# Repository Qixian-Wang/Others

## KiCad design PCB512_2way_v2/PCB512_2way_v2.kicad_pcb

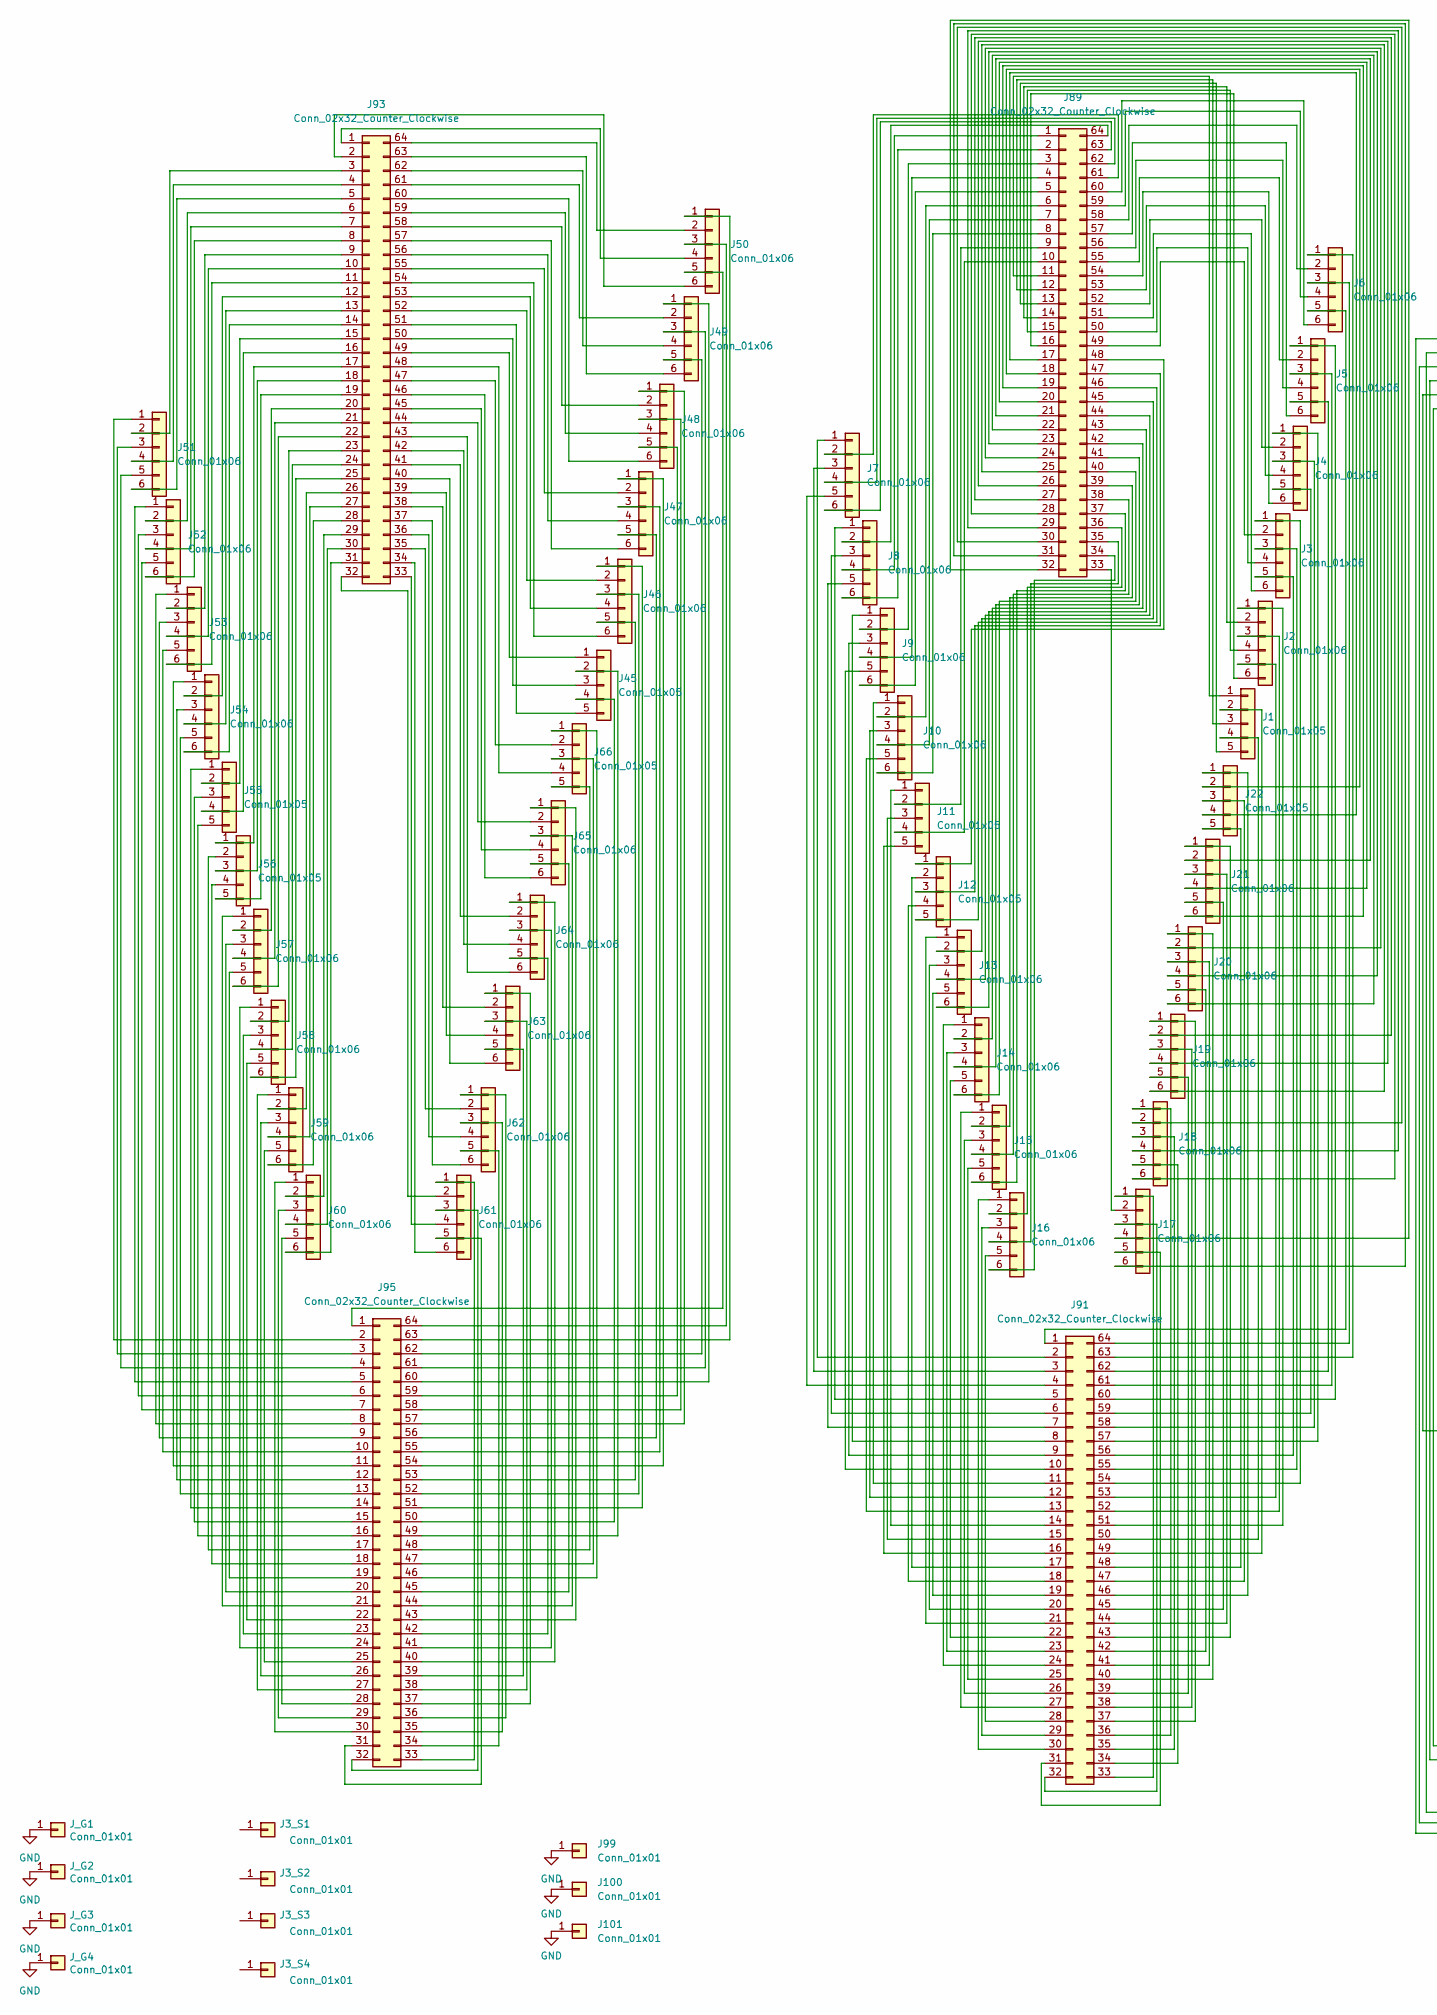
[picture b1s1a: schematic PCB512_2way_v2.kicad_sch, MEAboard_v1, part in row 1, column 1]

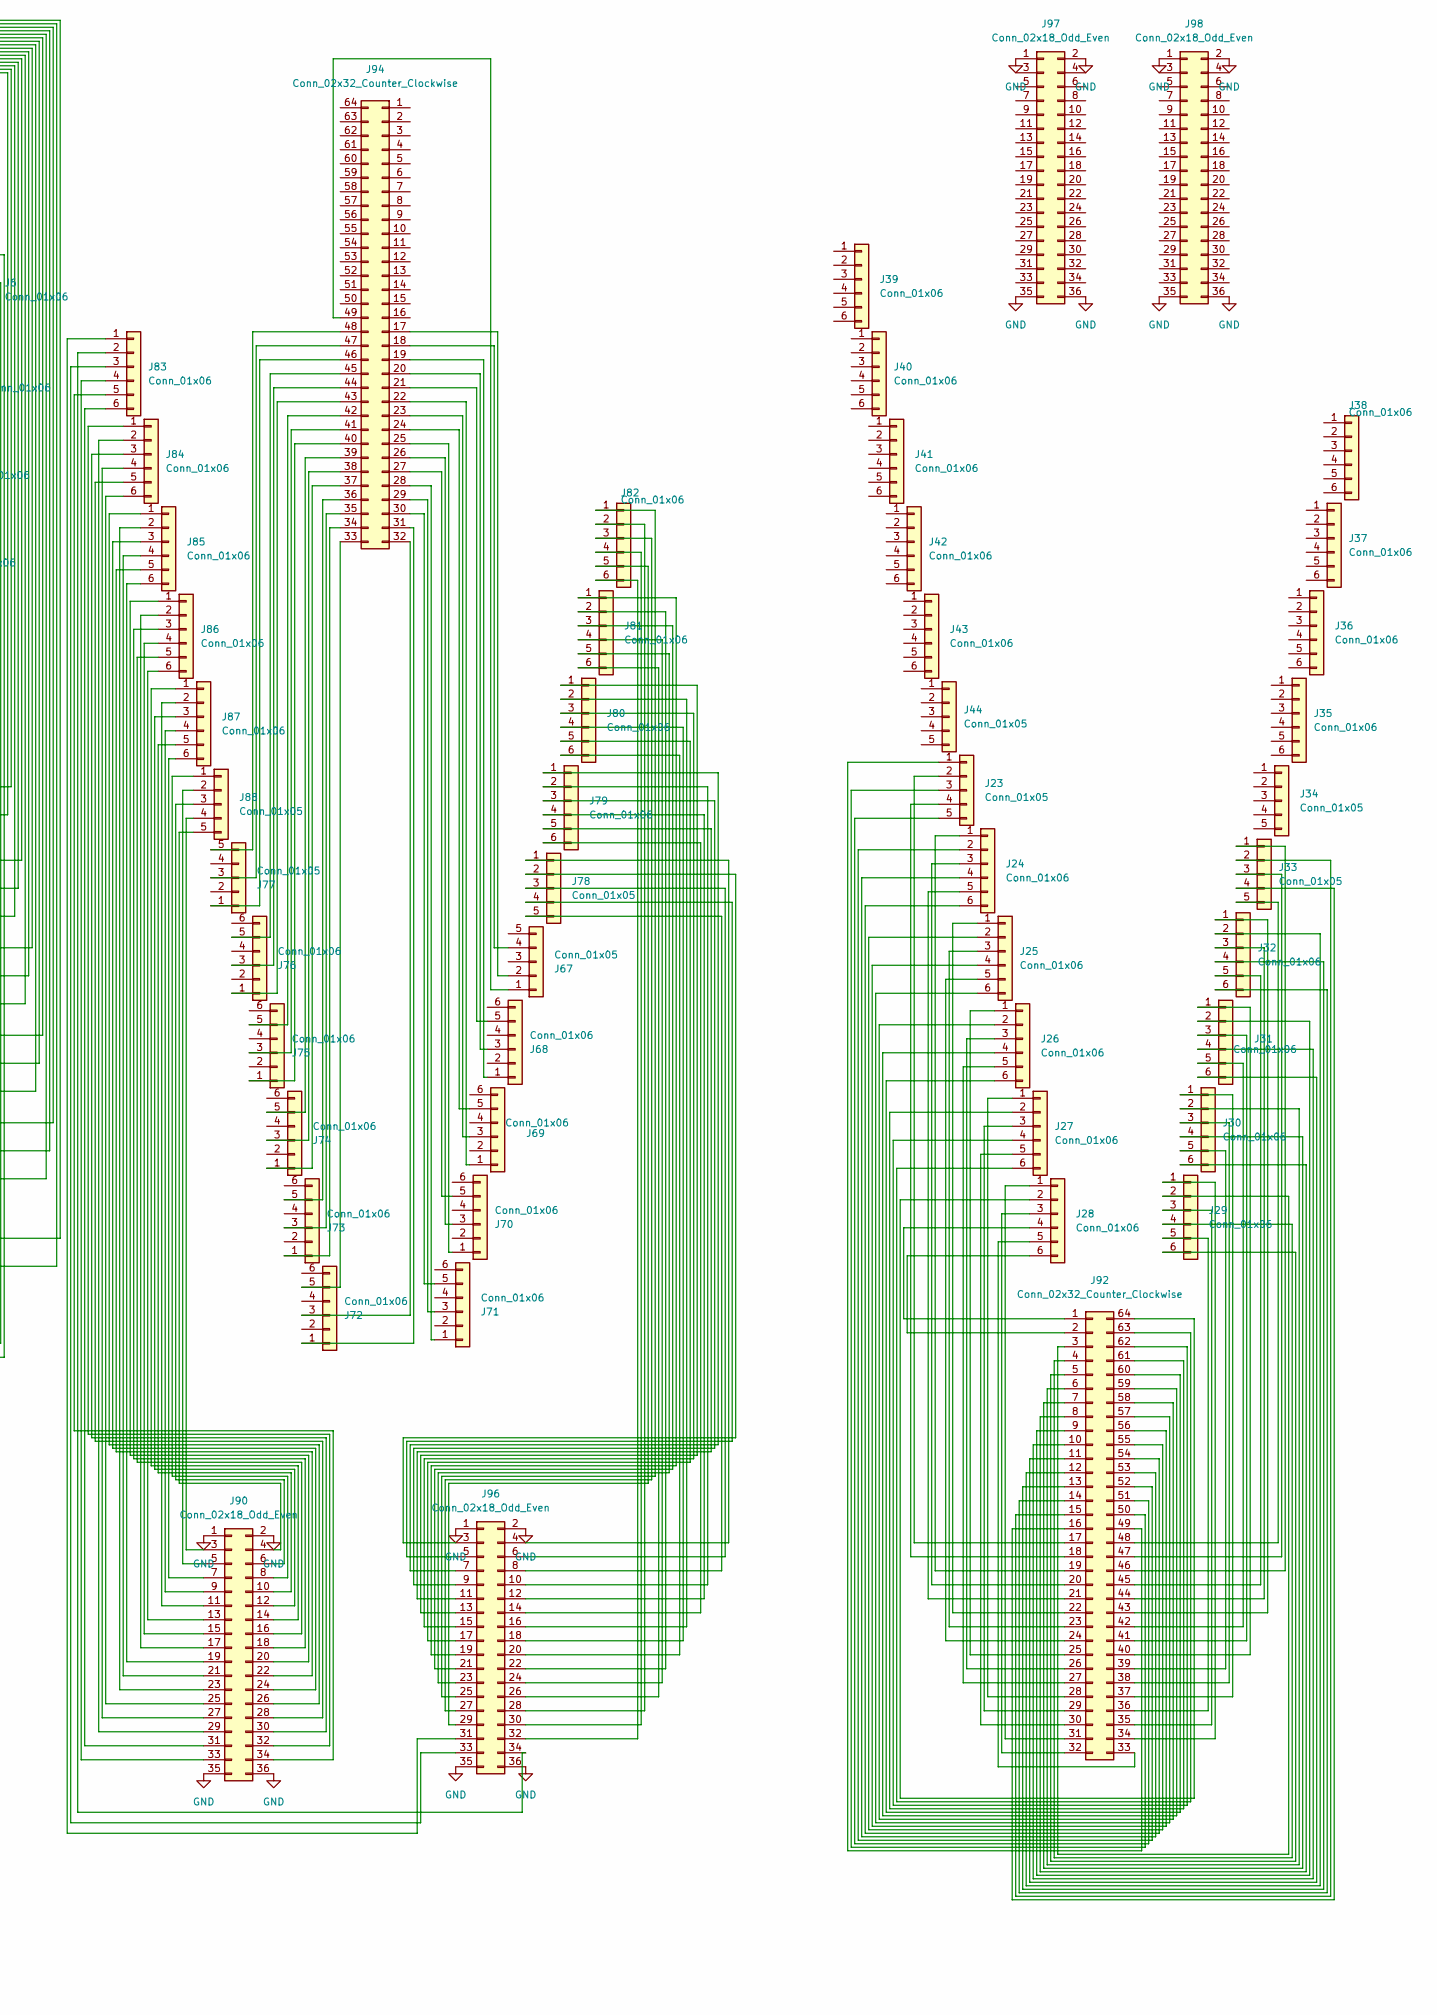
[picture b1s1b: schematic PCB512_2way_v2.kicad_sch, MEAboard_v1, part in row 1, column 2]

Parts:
J1, J11, J12, J22, J23, J33, J34, J44, J45, J55, J56, J66, J67, J77, J78, J88: Conn_01x05; PinHeader_1x05_P1.5mm_Vertical
J2, J3, J4, J5, J6, J7, J8, J9, J10, J13, J14, J15, J16, J17, J18, J19, J20, J21, J24, J25, J26, J27, J28, J29, J30, J31, J32, J35, J36, J37, J38, J39, J40, J41, J42, J43, J46, J47, J48, J49, J50, J51, J52, J53, J54, J57, J58, J59, J60, J61, J62, J63, J64, J65, J68, J69, J70, J71, J72, J73, J74, J75, J76, J79, J80, J81, J82, J83, J84, J85, J86, J87: Conn_01x06; PinHeader_1x06_P1.5mm_Vertical
J3_S1, J3_S2, J3_S3, J3_S4: Conn_01x01; PinHeader_1x01_P1.27mm_Vertical_0.483_STIM
J89, J91, J92, J93: Conn_02x32_Counter_Clockwise; PinHeader_2x32_P0.4mm_Vertical_SMD_Molex_Back
J90, J98: Conn_02x18_Odd_Even; PinHeader_2x18_Omnetics_Vertical_Hole_SMD_right_back
J94, J95: Conn_02x32_Counter_Clockwise; PinHeader_2x32_P0.4mm_Vertical_SMD_Molex
J96, J97: Conn_02x18_Odd_Even; PinHeader_2x18_Omnetics_Vertical_Hole_SMD_left_back
J99, J100, J101: Conn_01x01; PinSocket_1x01_P1.27mm_Vertical
J_G1, J_G2, J_G3, J_G4: Conn_01x01; PinHeader_1x01_P1.27mm_Vertical_0.483_GND

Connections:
GND: J90.1, J90.2, J90.35, J90.36, J96.1, J96.2, J96.35, J96.36, J97.1, J97.2, J97.35, J97.36, J98.1, J98.2, J98.35, J98.36, J99.1, J100.1, J101.1, J_G1.1, J_G2.1, J_G3.1, J_G4.1; also elsewhere on the board
unnamed: J1.1, J89.11
unnamed: J1.2, J91.49
unnamed: J1.3, J89.12
unnamed: J1.4, J91.50
unnamed: J1.5, J89.13
unnamed: J2.1, J91.51
unnamed: J2.2, J89.14
unnamed: J2.3, J91.52
unnamed: J2.4, J89.15
unnamed: J2.5, J91.53
unnamed: J2.6, J89.16
unnamed: J3.1, J91.54
unnamed: J3.2, J89.49
unnamed: J3.3, J91.55
unnamed: J3.4, J89.50
unnamed: J3.5, J91.56
unnamed: J3.6, J89.51
unnamed: J4.1, J91.57
unnamed: J4.2, J89.52
unnamed: J4.3, J91.58
unnamed: J4.4, J89.53
unnamed: J4.5, J91.59
unnamed: J4.6, J89.54
unnamed: J5.1, J91.60
unnamed: J5.2, J89.55
unnamed: J5.3, J91.61
unnamed: J5.4, J89.56
unnamed: J5.5, J91.62
unnamed: J5.6, J89.57
unnamed: J6.1, J91.63
unnamed: J6.2, J89.58
unnamed: J6.3, J91.64
unnamed: J6.4, J89.59
unnamed: J6.5, J91.1
unnamed: J6.6, J89.60
unnamed: J7.1, J91.2
unnamed: J7.2, J89.61
unnamed: J7.3, J91.3
unnamed: J7.4, J89.62
unnamed: J7.5, J91.4
unnamed: J7.6, J89.63
unnamed: J8.1, J91.5
unnamed: J8.2, J89.64
unnamed: J8.3, J91.6
unnamed: J8.4, J89.1
unnamed: J8.5, J91.7
unnamed: J8.6, J89.2
unnamed: J9.1, J91.8
unnamed: J9.3, J91.9
unnamed: J9.5, J91.10
unnamed: J10.1, J91.11
unnamed: J10.2, J89.6
unnamed: J10.3, J91.12
unnamed: J10.4, J89.7
unnamed: J10.5, J91.13
unnamed: J10.6, J89.8
unnamed: J11.1, J91.14
unnamed: J11.2, J89.9
unnamed: J11.3, J91.15
unnamed: J11.4, J89.10
unnamed: J11.5, J91.16
unnamed: J12.1, J89.48
unnamed: J12.2, J91.17
unnamed: J12.3, J89.47
unnamed: J12.4, J91.18
unnamed: J12.5, J89.46
unnamed: J13.1, J91.21
unnamed: J13.2, J89.45
unnamed: J13.3, J91.20
unnamed: J13.4, J89.44
unnamed: J13.5, J91.19
unnamed: J13.6, J89.43
unnamed: J14.1, J91.24
unnamed: J14.2, J89.42
unnamed: J14.3, J91.23
unnamed: J14.4, J89.41
unnamed: J14.5, J91.22
unnamed: J14.6, J89.40
unnamed: J15.1, J91.27
unnamed: J15.2, J89.39
unnamed: J15.3, J91.26
unnamed: J15.4, J89.38
unnamed: J15.5, J91.25
unnamed: J15.6, J89.37
unnamed: J16.1, J91.30
unnamed: J16.2, J89.36
unnamed: J16.3, J91.29
unnamed: J16.4, J89.35
unnamed: J16.5, J91.28
unnamed: J16.6, J89.34
unnamed: J17.1, J91.33
unnamed: J17.2, J89.33
unnamed: J17.3, J91.32
unnamed: J17.4, J89.32
unnamed: J17.5, J91.31
unnamed: J17.6, J89.31
unnamed: J18.1, J91.36
unnamed: J18.2, J89.30
unnamed: J18.3, J91.35
unnamed: J18.4, J89.29
unnamed: J18.5, J91.34
unnamed: J18.6, J89.28
unnamed: J19.1, J91.37
unnamed: J19.2, J89.27
unnamed: J19.3, J91.38
unnamed: J19.4, J89.26
unnamed: J19.5, J91.39
unnamed: J19.6, J89.25
unnamed: J20.1, J91.40
unnamed: J20.2, J89.24
unnamed: J20.3, J91.41
unnamed: J20.4, J89.23
unnamed: J20.5, J91.42
unnamed: J20.6, J89.22
unnamed: J21.1, J91.43
unnamed: J21.2, J89.21
unnamed: J21.3, J91.44
unnamed: J21.4, J89.20
unnamed: J21.5, J91.45
unnamed: J21.6, J89.19
unnamed: J22.1, J91.46
unnamed: J22.2, J89.18
unnamed: J22.3, J91.47
unnamed: J22.4, J89.17
unnamed: J22.5, J91.48
unnamed: J23.1, J92.49
unnamed: J23.2, J92.17
unnamed: J23.3, J92.50
unnamed: J23.4, J92.18
unnamed: J23.5, J92.51
unnamed: J24.1, J92.19
unnamed: J24.2, J92.52
unnamed: J24.3, J92.20
unnamed: J24.4, J92.53
unnamed: J24.5, J92.21
unnamed: J24.6, J92.54
unnamed: J25.1, J92.22
unnamed: J25.2, J92.55
unnamed: J25.3, J92.23
unnamed: J25.4, J92.56
unnamed: J25.5, J92.24
unnamed: J25.6, J92.57
unnamed: J26.1, J92.25
unnamed: J26.2, J92.58
unnamed: J26.3, J92.26
unnamed: J26.4, J92.59
unnamed: J26.5, J92.27
unnamed: J26.6, J92.60
unnamed: J27.1, J92.28
unnamed: J27.2, J92.61
unnamed: J27.3, J92.29
unnamed: J27.4, J92.62
unnamed: J27.5, J92.30
unnamed: J27.6, J92.63
unnamed: J28.1, J92.31
unnamed: J28.2, J92.64
unnamed: J28.3, J92.32
unnamed: J28.4, J92.1
unnamed: J28.5, J92.33
unnamed: J28.6, J92.2
unnamed: J29.1, J92.34
unnamed: J29.2, J92.3
unnamed: J29.3, J92.35
unnamed: J29.4, J92.4
unnamed: J29.5, J92.36
unnamed: J29.6, J92.5
unnamed: J30.1, J92.37
unnamed: J30.2, J92.6
unnamed: J30.3, J92.38
unnamed: J30.4, J92.7
unnamed: J30.5, J92.39
unnamed: J30.6, J92.8
unnamed: J31.1, J92.40
unnamed: J31.2, J92.9
unnamed: J31.3, J92.41
unnamed: J31.4, J92.10
unnamed: J31.5, J92.42
unnamed: J31.6, J92.11
unnamed: J32.1, J92.43
unnamed: J32.2, J92.12
unnamed: J32.3, J92.44
unnamed: J32.4, J92.13
unnamed: J32.5, J92.45
unnamed: J32.6, J92.14
unnamed: J33.1, J92.46
unnamed: J33.2, J92.15
unnamed: J33.3, J92.47
unnamed: J33.4, J92.16
unnamed: J33.5, J92.48
unnamed: J45.1, J93.49
unnamed: J45.2, J95.49
unnamed: J45.3, J93.50
unnamed: J45.4, J95.50
unnamed: J45.5, J93.51
unnamed: J46.1, J95.51
unnamed: J46.2, J93.52
unnamed: J46.3, J95.52
unnamed: J46.4, J93.53
unnamed: J46.5, J95.53
unnamed: J46.6, J93.54
unnamed: J47.1, J95.54
unnamed: J47.2, J93.55
unnamed: J47.3, J95.55
unnamed: J47.4, J93.56
unnamed: J47.5, J95.56
unnamed: J47.6, J93.57
unnamed: J48.1, J95.57
unnamed: J48.2, J93.58
unnamed: J48.3, J95.58
unnamed: J48.4, J93.59
unnamed: J48.5, J95.59
unnamed: J48.6, J93.60
unnamed: J49.1, J95.60
unnamed: J49.2, J93.61
unnamed: J49.3, J95.61
unnamed: J49.4, J93.62
unnamed: J49.5, J95.62
unnamed: J49.6, J93.63
unnamed: J50.1, J95.63
unnamed: J50.2, J93.64
unnamed: J50.3, J95.64
unnamed: J50.4, J93.1
unnamed: J50.5, J95.1
unnamed: J50.6, J93.2
unnamed: J51.1, J95.2
unnamed: J51.2, J93.3
unnamed: J51.3, J95.3
unnamed: J51.4, J93.4
unnamed: J51.5, J95.4
unnamed: J51.6, J93.5
unnamed: J52.1, J95.5
unnamed: J52.2, J93.6
unnamed: J52.3, J95.6
unnamed: J52.4, J93.7
unnamed: J52.5, J95.7
unnamed: J52.6, J93.8
unnamed: J53.1, J95.8
unnamed: J53.2, J93.9
unnamed: J53.3, J95.9
unnamed: J53.4, J93.10
unnamed: J53.5, J95.10
unnamed: J53.6, J93.11
unnamed: J54.1, J95.11
unnamed: J54.2, J93.12
unnamed: J54.3, J95.12
unnamed: J54.4, J93.13
unnamed: J54.5, J95.13
unnamed: J54.6, J93.14
unnamed: J55.1, J95.14
unnamed: J55.2, J93.15
unnamed: J55.3, J95.15
unnamed: J55.4, J93.16
unnamed: J55.5, J95.16
unnamed: J56.1, J93.17
unnamed: J56.2, J95.17
unnamed: J56.3, J93.18
unnamed: J56.4, J95.18
unnamed: J56.5, J93.19
unnamed: J57.1, J95.21
unnamed: J57.2, J93.20
unnamed: J57.3, J95.20
unnamed: J57.4, J93.21
unnamed: J57.5, J95.19
unnamed: J57.6, J93.22
unnamed: J58.1, J95.24
unnamed: J58.2, J93.23
unnamed: J58.3, J95.23
unnamed: J58.4, J93.24
unnamed: J58.5, J95.22
unnamed: J58.6, J93.25
unnamed: J59.1, J95.27
unnamed: J59.2, J93.26
unnamed: J59.3, J95.26
unnamed: J59.4, J93.27
unnamed: J59.5, J95.25
unnamed: J59.6, J93.28
unnamed: J60.1, J95.30
unnamed: J60.2, J93.29
unnamed: J60.3, J95.29
unnamed: J60.4, J93.30
unnamed: J60.5, J95.28
unnamed: J60.6, J93.31
unnamed: J61.1, J95.33
unnamed: J61.2, J93.32
unnamed: J61.3, J95.32
unnamed: J61.4, J93.33
unnamed: J61.5, J95.31
unnamed: J61.6, J93.34
unnamed: J62.1, J95.36
unnamed: J62.2, J93.35
unnamed: J62.3, J95.35
unnamed: J62.4, J93.36
unnamed: J62.5, J95.34
unnamed: J62.6, J93.37
unnamed: J63.1, J95.37
unnamed: J63.2, J93.38
unnamed: J63.3, J95.38
unnamed: J63.4, J93.39
unnamed: J63.5, J95.39
unnamed: J63.6, J93.40
unnamed: J64.1, J95.40
unnamed: J64.2, J93.41
unnamed: J64.3, J95.41
unnamed: J64.4, J93.42
unnamed: J64.5, J95.42
unnamed: J64.6, J93.43
unnamed: J65.1, J95.43
unnamed: J65.2, J93.44
unnamed: J65.3, J95.44
unnamed: J65.4, J93.45
unnamed: J65.5, J95.45
unnamed: J65.6, J93.46
unnamed: J66.1, J95.46
unnamed: J66.2, J93.47
unnamed: J66.3, J95.47
unnamed: J66.4, J93.48
unnamed: J66.5, J95.48
unnamed: J67.1, J94.49
unnamed: J67.2, J94.17
unnamed: J67.4, J94.18
unnamed: J68.1, J94.19
unnamed: J68.3, J94.20
unnamed: J68.5, J94.21
unnamed: J69.1, J94.22
unnamed: J69.3, J94.23
unnamed: J69.5, J94.24
unnamed: J70.1, J94.25
unnamed: J70.3, J94.26
unnamed: J70.5, J94.27
unnamed: J71.1, J94.28
unnamed: J71.3, J94.29
unnamed: J71.5, J94.30
unnamed: J72.1, J94.31
unnamed: J72.3, J94.32
unnamed: J72.5, J94.33
unnamed: J73.1, J94.34
unnamed: J73.3, J94.35
unnamed: J73.5, J94.36
unnamed: J74.1, J94.37
unnamed: J74.3, J94.38
unnamed: J74.5, J94.39
unnamed: J75.1, J94.40
unnamed: J75.3, J94.41
unnamed: J75.5, J94.42
unnamed: J76.1, J94.43
unnamed: J76.3, J94.44
unnamed: J76.5, J94.45
unnamed: J77.1, J94.46
unnamed: J77.3, J94.47
unnamed: J77.5, J94.48
unnamed: J78.1, J96.4
unnamed: J78.2, J96.3
unnamed: J78.3, J96.6
unnamed: J78.4, J96.5
unnamed: J78.5, J96.8
unnamed: J79.1, J96.7
unnamed: J79.2, J96.10
unnamed: J79.3, J96.9
unnamed: J79.4, J96.12
unnamed: J79.5, J96.11
unnamed: J79.6, J96.14
unnamed: J80.1, J96.13
unnamed: J80.2, J96.16
unnamed: J80.3, J96.15
unnamed: J80.4, J96.18
unnamed: J80.5, J96.17
unnamed: J80.6, J96.20
unnamed: J81.1, J96.19
unnamed: J81.2, J96.22
unnamed: J81.3, J96.21
unnamed: J81.4, J96.24
unnamed: J81.5, J96.23
unnamed: J81.6, J96.26
unnamed: J82.1, J96.25
unnamed: J82.2, J96.28
unnamed: J82.3, J96.27
unnamed: J82.4, J96.30
unnamed: J82.5, J96.29
unnamed: J82.6, J96.32
unnamed: J83.1, J96.31
unnamed: J83.2, J96.34
unnamed: J83.3, J96.33
unnamed: J83.4, J90.33
unnamed: J83.5, J90.34
unnamed: J83.6, J90.31
unnamed: J84.1, J90.32
unnamed: J84.2, J90.29
unnamed: J84.3, J90.30
unnamed: J84.4, J90.27
unnamed: J84.5, J90.28
unnamed: J84.6, J90.25
unnamed: J85.1, J90.26
unnamed: J85.2, J90.23
unnamed: J85.3, J90.24
unnamed: J85.4, J90.21
unnamed: J85.5, J90.22
unnamed: J85.6, J90.19
unnamed: J86.1, J90.20
unnamed: J86.2, J90.17
unnamed: J86.3, J90.18
unnamed: J86.4, J90.15
unnamed: J86.5, J90.16
unnamed: J86.6, J90.13
unnamed: J87.1, J90.14
unnamed: J87.2, J90.11
unnamed: J87.3, J90.12
unnamed: J87.4, J90.9
unnamed: J87.5, J90.10
unnamed: J87.6, J90.7
unnamed: J88.1, J90.8
unnamed: J88.2, J90.5
unnamed: J88.3, J90.6
unnamed: J88.4, J90.3
unnamed: J88.5, J90.4
unnamed: J9.2, J89.3
unnamed: J9.4, J89.4
unnamed: J9.6, J89.5

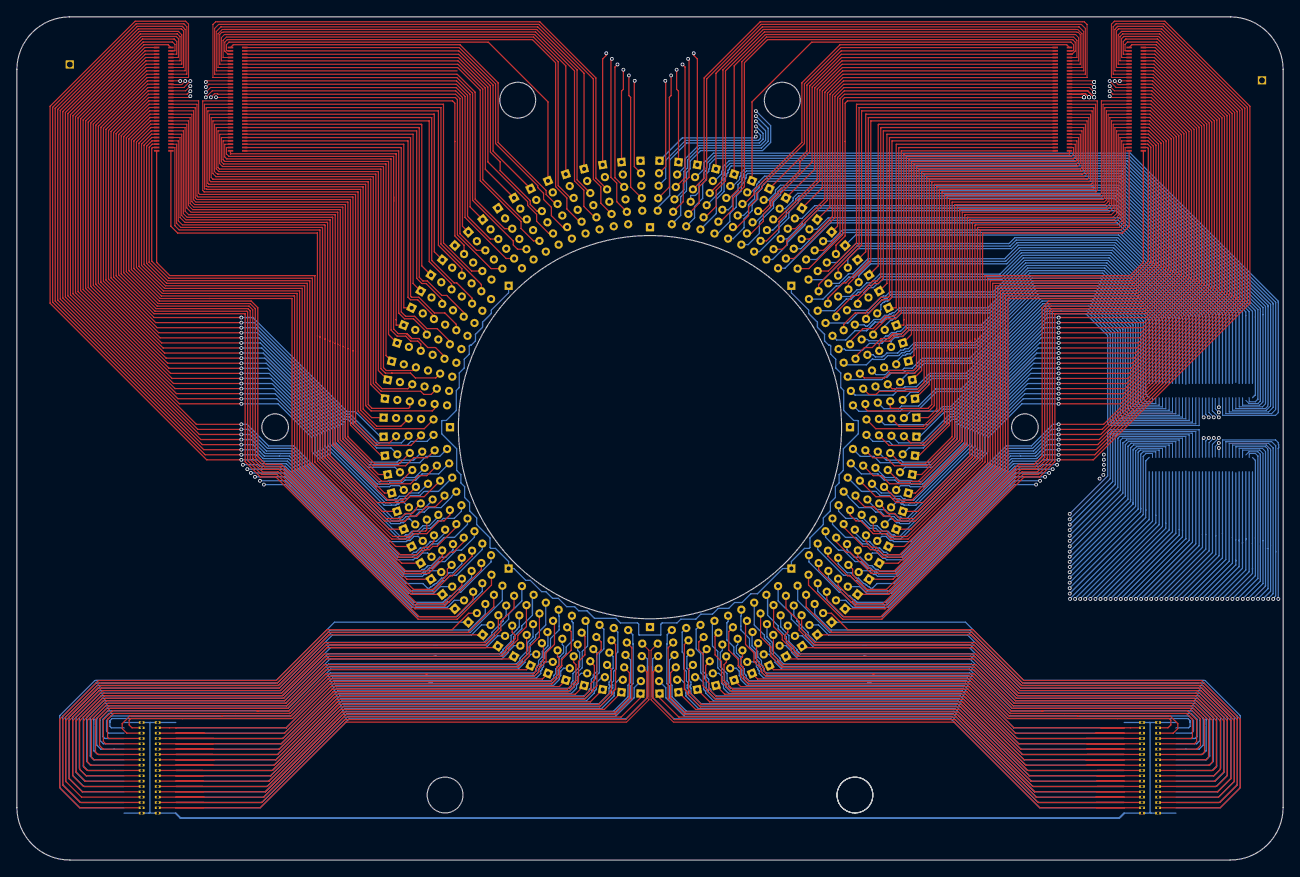
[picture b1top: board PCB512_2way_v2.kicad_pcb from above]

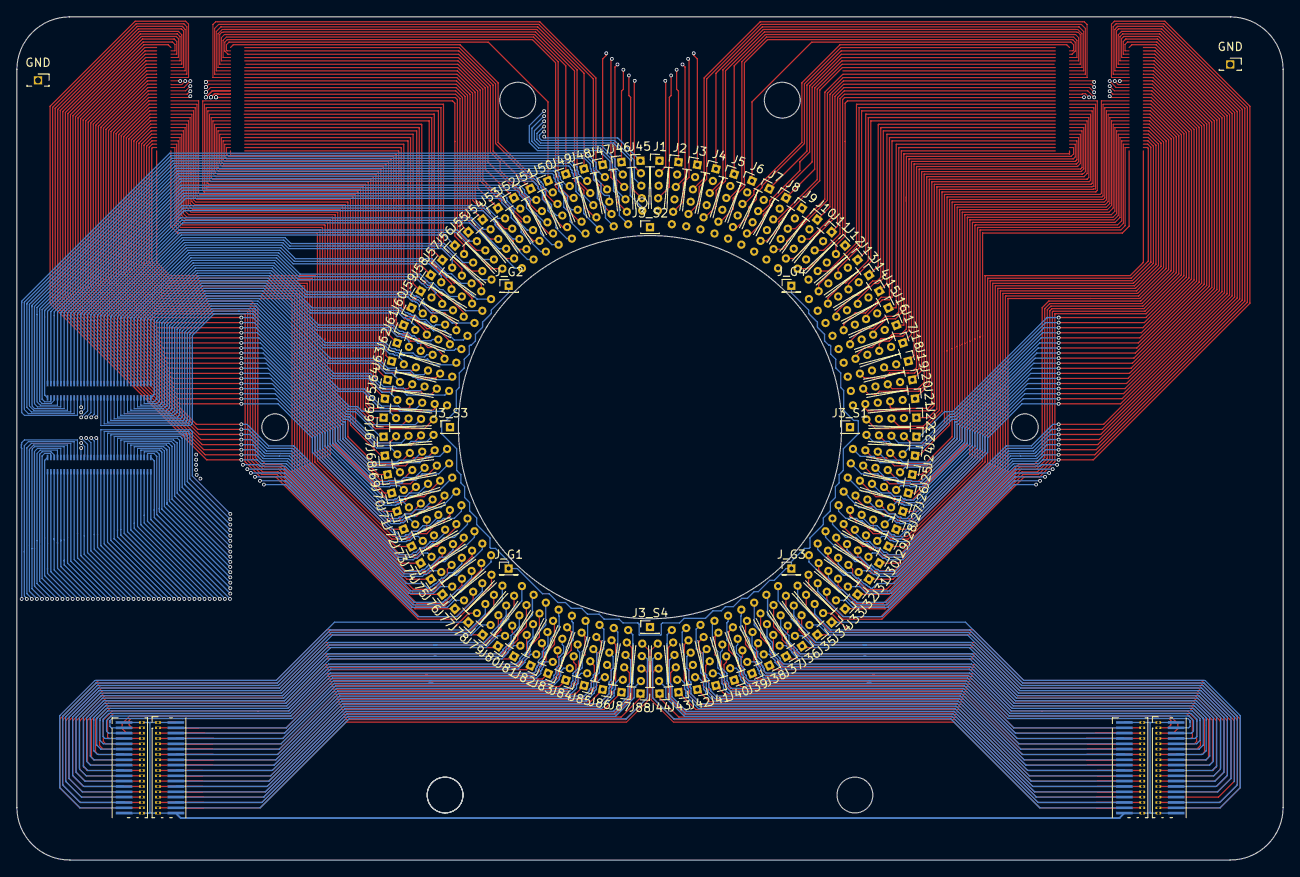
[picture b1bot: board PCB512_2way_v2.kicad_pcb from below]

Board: 4 copper layers, 152.0 x 101.2 mm, 108 parts (104 on the bottom side), 418 nets.

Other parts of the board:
GND: Conn_01x01; PinSocket_1x01_P1.27mm_Vertical
GND#2: Conn_01x01; PinSocket_1x01_P1.27mm_Vertical

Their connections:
GND: GND.1, GND#2.1; also elsewhere on the board

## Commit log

2025-02-07 使用 Colab 创建而成
2025-05-07 Created using Colab
2025-07-19 Add intro to file management
2025-07-19 correct typo
2025-07-19 modify code
2025-11-09 Add MEAfab.md with spin coating and lithography steps
2025-11-09 Change headers from '#' to '###' in MEAfab.md
2025-11-09 Add E-beam and Lift-off sections to MEAfab.md
    Added E-beam and Lift-off sections with instructions.
2025-11-11 Fix exposure mode formatting and add dose details
    Correct exposure mode format and add dose information.
2025-11-12 Add RIE process instructions to MEAfab.md
    Added instructions for RIE process and multimeter usage.
2025-11-22 Document steps to build OE plugin
    Added detailed steps for building the OE plugin using Visual Studio.
2025-11-22 Rename Build OE plugin to Build OE plugin.md
